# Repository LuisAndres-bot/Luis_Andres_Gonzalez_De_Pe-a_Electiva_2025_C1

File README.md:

# Luis_Andres_Gonzalez_De_Pe-a_Electiva_2025_C1
Repositorio de Git para la asignatura de Electiva

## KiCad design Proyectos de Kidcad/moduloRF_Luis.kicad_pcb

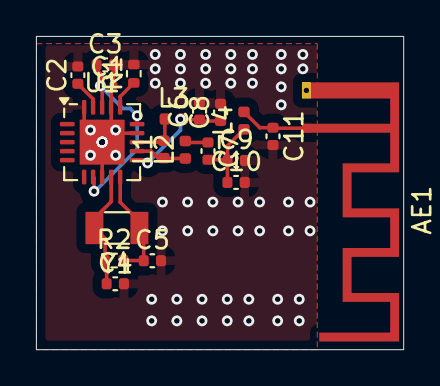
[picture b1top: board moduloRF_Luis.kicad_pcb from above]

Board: 2 copper layers, 20.4 x 17.4 mm, 20 parts (0 on the bottom side), 12 nets.

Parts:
AE1: Antenna; Texas_SWRA117D_2.4GHz_Right
C1: 10n; C_0201_0603Metric
C2: 33n; C_0402_1005Metric
C3: 1n; C_0402_1005Metric
C4, C5: 22p; C_0402_1005Metric
C6, C8: C_Small; C_0402_1005Metric
C7: 1p5; C_0402_1005Metric
C9: 1p; C_0402_1005Metric
C10, C11: Cx; C_0402_1005Metric
L1: 8n2; L_0402_1005Metric
L2: 3n9; L_0402_1005Metric
L3: 2n7; L_0402_1005Metric
L4: Lx; L_0402_1005Metric
R1: 22k; R_0402_1005Metric
R2: 16MHz; R_0402_1005Metric
U1: NRF24L01; QFN-20-1EP_4x4mm_P0.5mm_EP2.5x2.5mm
Y1: Crystal; Crystal_SMD_3215-2Pin_3.2x1.5mm

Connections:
GND: C1.2, C2.2, C3.2, C4.2, C5.2, C6.2, C8.2, C9.2, C10.2, C11.2, R1.2, U1.8 (VSS), U1.14 (VSS), U1.17 (VSS), U1.20 (VSS), U1.21
unnamed: AE1.1 (A), C11.1, L4.2
unnamed: C7.1, L2.2
unnamed: C7.2, C9.1, C10.1, L4.1
unnamed: L1.1, L2.1, U1.12 (ANT1)
unnamed: L1.2, L3.1, U1.13 (ANT2)
unnamed: C2.1, U1.19 (DVDD)
unnamed: R1.1, U1.16 (IREF)
unnamed: C6.1, C8.1, L3.2, U1.11 (VDD_PA)
unnamed: C5.1, R2.2, U1.10 (XC1), Y1.2
unnamed: C4.1, R2.1, U1.9 (XC2), Y1.1
VDD: C1.1, C3.1, U1.7 (VDD), U1.15 (VDD), U1.18 (VDD)

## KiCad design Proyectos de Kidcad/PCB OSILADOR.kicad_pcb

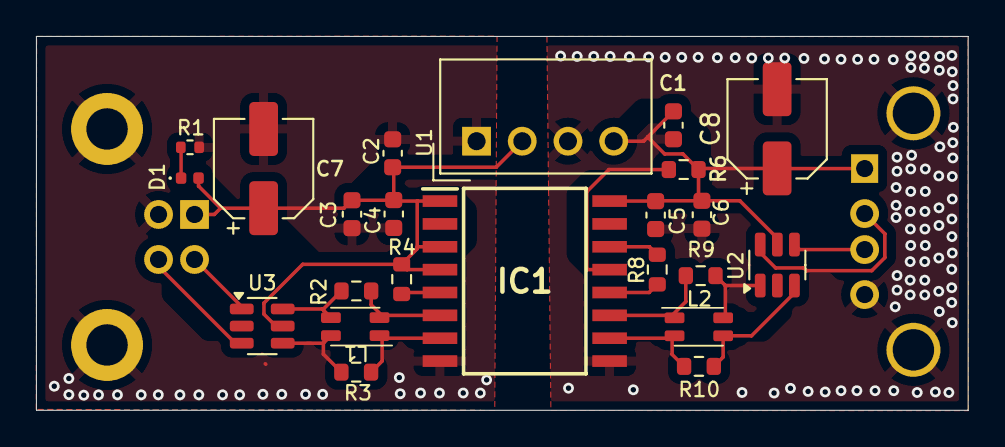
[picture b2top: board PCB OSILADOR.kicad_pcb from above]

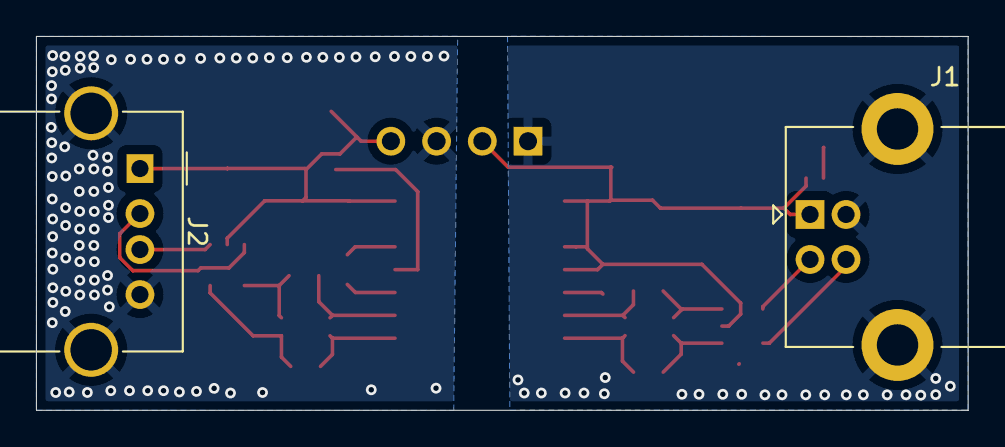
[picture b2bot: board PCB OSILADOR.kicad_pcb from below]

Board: 2 copper layers, 51.8 x 20.8 mm, 25 parts (2 on the bottom side), 21 nets.

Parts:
C1, C2: C; C_0603_1608Metric
C3, C4, C5, C6: 100nF; C_0603_1608Metric
C7, C8: C; CP_Elec_5x5.4
D1: LED; LED_0402_1005Metric
IC1: ADUM3160BRWZ; SOIC127P1032X265-16N
J1: USB_B; USB_B_Lumberg_2411_02_Horizontal
J2: USB_A; USB_A_Molex_67643_Horizontal
L1, L2: Choke_Wurth_WE-CNSW_744232090; L_CommonMode_Wurth_WE-CNSW-1206
R1: R; R_0402_1005Metric
R2, R8, R9: 0ohm; R_0603_1608Metric
R3, R4, R6, R10: 0 ohm; R_0603_1608Metric
U1: TME-0505S; Converter_DCDC_TRACO_TME_03xxS_05xxS_12xxS_Single_THT
U2, U3: USBLC6-2SC6; SOT-23-6

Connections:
+5V: C2.1, C3.1, C4.1, C7.1, D1.2 (A), IC1.1 (VBUS1), IC1.3 (VDD1), IC1.4 (PDEN), J1.1 (VBUS), R4.2, U1.2 (+Vin), U3.5 (VBUS)
D+: J1.3 (D+), U3.3 (I/O2)
D-: J1.2 (D-), U3.1 (I/O1)
DD_+: IC1.10 (DD+), L2.4, R10.1
DD_-: IC1.11 (DD-), L2.1, R9.1
GND1: C2.2, C3.2, C4.2, C7.2, IC1.2 (GND1_1), IC1.8 (GND1_2), J1.4 (GND), J1.5 (Shield), R1.2, U1.1 (-Vin), U3.2 (GND)
GND2: C1.2, C5.2, C6.2, C8.2, IC1.9 (GND2_1), IC1.15 (GND2_2), J2.4 (GND), J2.5 (Shield), U1.3 (-Vout), U2.2 (GND)
L1_+: IC1.7 (UD+), L1.1, R3.2
L1_-: IC1.6 (UD-), L1.4, R2.2
L2_+: L2.3, R10.2, U2.3 (I/O2)
L2_-: L2.2, R9.2, U2.1 (I/O1)
unnamed: D1.1 (K), R1.1
unnamed: IC1.12 (PIN), R8.2
unnamed: IC1.13 (SPD), R6.1
unnamed: IC1.5 (SPU), R4.1
unnamed: IC1.14 (VDD2), R8.1
U2_+: J2.3 (D+), U2.4 (I/O2)
U2_-: J2.2 (D-), U2.6 (I/O1)
U3_+: L1.2, R3.1, U3.4 (I/O2)
U3_-: L1.3, R2.1, U3.6 (I/O1)
VDD: C1.1, C5.1, C6.1, C8.1, IC1.16 (VBUS2), J2.1 (VBUS), R6.2, U1.4 (+Vout), U2.5 (VBUS)

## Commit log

2025-04-25 Create Resumen del capitulo 1 y 2
2025-04-25 Create Tarea 1 comando de GIT
2025-04-25 Update Tarea 1 comando de GIT
2025-04-25 Create Comando push
2025-04-25 Create Comando pull
2025-04-25 Create Comando commit
2025-04-25 Create Comando branch
2025-04-25 Comando fetch
2025-04-25 Create Comando tag
2025-04-25 Create Proyecto 1 Kicad
2025-04-26 Create Comando de Github
